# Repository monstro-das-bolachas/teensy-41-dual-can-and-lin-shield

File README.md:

# OBDee-Wan CANobi

> Open-hardware automotive bus interface for CAN FD, classic CAN, LIN, and K-line exploration.

OBDee-Wan CANobi is a Teensy 4.1 based vehicle-network tool for hackers, makers, reverse engineers, EV converters, and curious learners who want hardware they can inspect and understand.

It is designed as a practical bridge between a laptop and a vehicle or bench module: powerful enough for real CAN FD/LIN/K-line experiments, but documented as a teaching project rather than a black box.

## At a glance

| Area | Current R11 target |
| --- | --- |
| Host | Teensy 4.1 |
| CAN FD | 2 external CAN FD controller paths |
| Transceivers | Dual CAN FD transceivers |
| Other buses | LIN / K-line support path |
| Vehicle connection | OBD pigtail-friendly wiring, not a direct-plug dongle |
| Configuration | DIP-switch selectable routing options |
| CAD | KiCad hardware source and generated fabrication packages |
| Readiness | Bare-PCB prototype candidate for bench bring-up |

## What you can use it for

- CAN FD experimentation and learning
- Classic CAN diagnostics and reverse engineering
- LIN and K-line bench experiments
- EV conversion support tooling
- Custom diagnostic interface development
- Teaching automotive networks with inspectable hardware
- Bench testing ECUs, modules, sensors, and harness fragments

## Current status: R11 prototype manufacturing candidate

R11 may be ordered as a small bare-PCB prototype batch for bench bring-up.

It is not approved for direct vehicle testing yet.

### Active release package

`revisions/00_WORK_R11_TRUE_DUAL_CANFD/release/R11_PROTOTYPE_MANUFACTURING_CANDIDATE_20260630/`

### Manufacturer upload ZIP

`revisions/00_WORK_R11_TRUE_DUAL_CANFD/release/R11_PROTOTYPE_MANUFACTURING_CANDIDATE_20260630/package/JLCPCB_PCBWAY_UPLOAD_R11_MINIMAL_GERBERS_ONLY_20260630.zip`

SHA256:

`434dedf475bb3443f1ffa6384541426fcef9cf96a792c1744b9c1bb7ff68faa8`

### Verification summary

| Check | Result |
| --- | --- |
| KiCad CLI PCB DRC | 0 violations |
| Footprint errors | 0 |
| Known residual | 1 GND zone-to-zone report at 1.0000 mm / 1.0000 mm |
| Gerber/drill export | Successful |
| GND continuity | Visually confirmed in KiCad after refill/highlight |
| Vehicle-use approval | Not yet; bench validation required first |

The remaining GND item is a reviewed KiCad zone-report artifact for prototype PCB ordering. It is not a blanket safety approval for vehicle connection.

## Safety first

Vehicle electrical systems can damage tools, modules, or the car if connected incorrectly. Treat every first assembly as experimental hardware.

Before connecting to a vehicle:

1. Inspect the bare PCB.
2. Check for rail shorts with a multimeter.
3. Assemble and test the power section first.
4. Power up from a current-limited bench supply.
5. Verify OBD/pigtail pin mapping manually.
6. Confirm DIP-switch defaults and intended routing.
7. Test CAN/LIN/K behavior on bench modules first.
8. Use fusing and current limiting for any later vehicle test.

## Repository map

| Path | Purpose |
| --- | --- |
| `README_START_HERE.txt` | Short navigation and safety guide |
| `CURRENT_STATUS.md` | Current revision status, ordering notes, and verification summary |
| `revisions/00_WORK_R11_TRUE_DUAL_CANFD/` | Active R11 prototype candidate source and release package |
| `revisions/00_ACTIVE_R10_TRUE_DUAL_CANFD/` | Previous R10 archive, not for fabrication |
| `revisions/01_R9_CLASSIC_CAN_ARCHIVE/` | Historical R9 classic-CAN reference |
| `LICENSE` | Main hardware license: CERN-OHL-P-2.0 |
| `LICENSES/` | Full license texts and license split documentation |

## Recommended first order

For the first prototype batch, use conservative bare-board settings:

| Option | Recommendation |
| --- | --- |
| Quantity | 5 or smallest economical batch |
| Layers | 2 |
| Material | FR-4 |
| Thickness | 1.6 mm |
| Copper | 1 oz |
| Surface finish | Standard low-cost prototype finish is acceptable |
| Electrical test | Yes |
| Assembly | No; hand-assemble and validate first |

## Naming note

The project name is a small joke:

OBDee-Wan CANobi: an OBD/CAN interface that helps you feel disturbances in the bus.

## License

This project is open source and open hardware.

| Content | License |
| --- | --- |
| Hardware design files, KiCad sources, PCB/manufacturing files | CERN-OHL-P-2.0 |
| Firmware, scripts, and software | MIT |
| Documentation | CC-BY-4.0 |

You are free to study, modify, build, remix, and share this project. Attribution is required where applicable: please credit the original project and author when reusing or publishing derivative work.

See `LICENSES/README.md` for the full license split and SPDX identifiers.

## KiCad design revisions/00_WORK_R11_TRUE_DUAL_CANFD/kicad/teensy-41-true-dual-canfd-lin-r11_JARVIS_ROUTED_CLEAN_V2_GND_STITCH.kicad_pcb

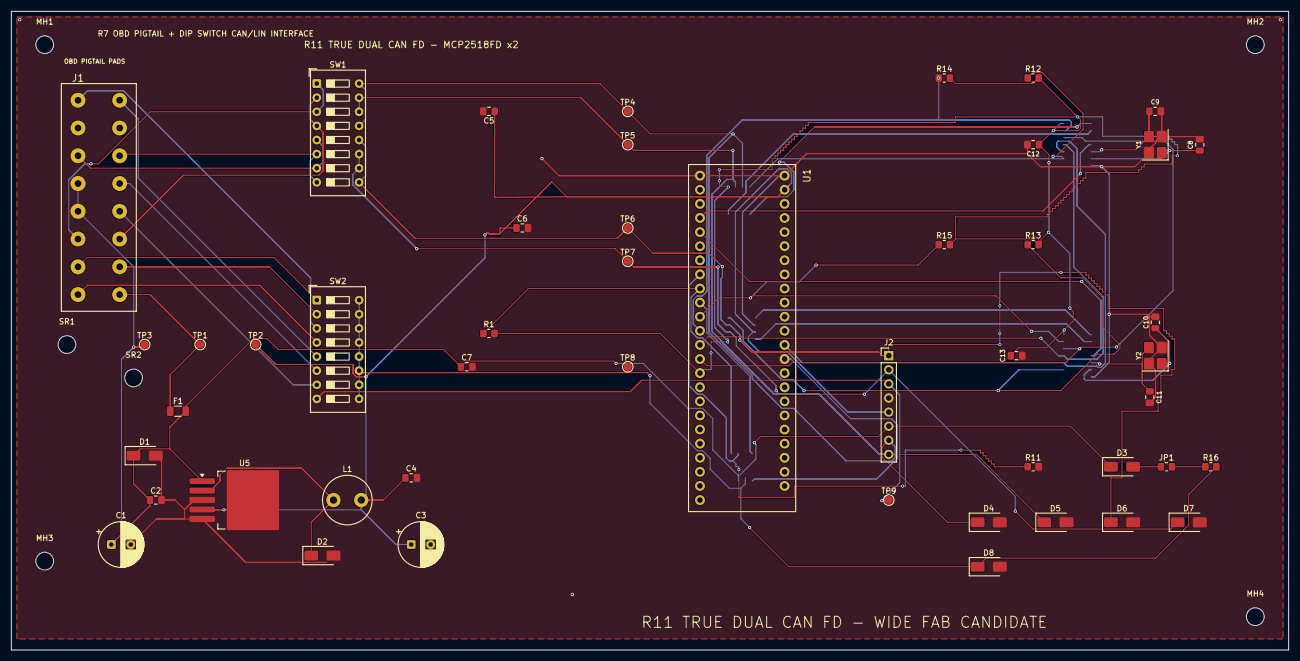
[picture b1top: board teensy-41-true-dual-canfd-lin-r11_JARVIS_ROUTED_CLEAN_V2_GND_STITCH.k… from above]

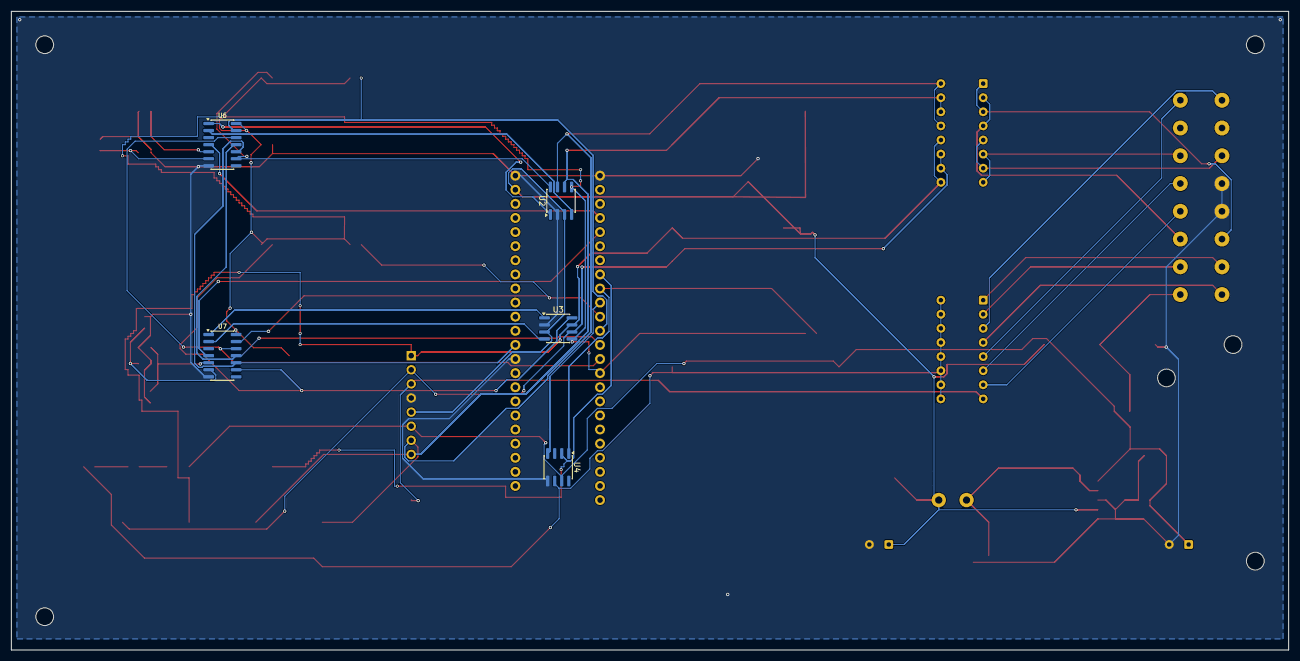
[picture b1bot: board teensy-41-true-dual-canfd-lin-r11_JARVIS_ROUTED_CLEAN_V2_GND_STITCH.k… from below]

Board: 2 copper layers, 230.0 x 115.0 mm, 59 parts (5 on the bottom side), 45 nets.

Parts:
C1: 100uF_50V_INPUT; CP_Radial_D8.0mm_P3.50mm
C2: 100nF_50V_INPUT; C_0805_2012Metric_Pad1.18x1.45mm_HandSolder
C3: 330uF_16V_OUTPUT_LOW_ESR; CP_Radial_D8.0mm_P3.50mm
C4: 100nF_16V_OUTPUT; C_0805_2012Metric_Pad1.18x1.45mm_HandSolder
C5: 100nF_CAN_A_VDD_LOCAL; C_0805_2012Metric_Pad1.18x1.45mm_HandSolder
C6: 100nF_CAN_B_VDD_LOCAL; C_0805_2012Metric_Pad1.18x1.45mm_HandSolder
C7: 100nF_LIN_VSUP_LOCAL; C_0805_2012Metric_Pad1.18x1.45mm_HandSolder
C8: 22pF_Y1_OSC1; C_0805_2012Metric_Pad1.18x1.45mm_HandSolder
C9: 22pF_Y1_OSC2; C_0805_2012Metric_Pad1.18x1.45mm_HandSolder
C10: 22pF_Y2_OSC1; C_0805_2012Metric_Pad1.18x1.45mm_HandSolder
C11: 22pF_Y2_OSC2; C_0805_2012Metric_Pad1.18x1.45mm_HandSolder
C12: 100nF_U6_VDD_LOCAL; C_0805_2012Metric_Pad1.18x1.45mm_HandSolder
C13: 100nF_U7_VDD_LOCAL; C_0805_2012Metric_Pad1.18x1.45mm_HandSolder
D1: SMBJ24CA_TVS_12V; D_SMA
D2: SS34_BUCK_SCHOTTKY; D_SMA
D3: LIN_MASTER_PULLUP_DIODE_DNP; D_SMA
D4: ESD_CAN_A_H_TVS_VERIFY; D_SMA
D5: ESD_CAN_A_L_TVS_VERIFY; D_SMA
D6: ESD_CAN_B_H_TVS_VERIFY; D_SMA
D7: ESD_CAN_B_L_TVS_VERIFY; D_SMA
D8: ESD_LIN_K_TVS_VERIFY; D_SMA
F1: POLYFUSE_500mA; Fuse_1206_3216Metric
J1: OBD2_PIGTAIL_16_WIRE_SOLDER_PADS; OBD2_PigtailPads_Manufacturing
J2: AUX_HEADER; PinHeader_1x08_P2.54mm_Vertical
JP1: LIN_MASTER_ENABLE_OPEN_0R_DNP; R_0805_2012Metric_Pad1.20x1.40mm_HandSolder
L1: 33uH_3A_BUCK_INDUCTOR; L_Radial_D8.7mm_P5.00mm_Fastron_07HCP
MH1, MH2, MH3, MH4: M3; MountingHole_3.2mm_M3
R1: 10k_LIN_RX_PULLUP; R_0805_2012Metric_Pad1.20x1.40mm_HandSolder
R11: 100k_LIN_EN_PULLDOWN; R_0805_2012Metric_Pad1.20x1.40mm_HandSolder
R12: 10k_CAN_A_STBY_PULLUP; R_0805_2012Metric_Pad1.20x1.40mm_HandSolder
R13: 10k_CAN_B_STBY_PULLUP; R_0805_2012Metric_Pad1.20x1.40mm_HandSolder
R14: 10k_CANFD_A_NCS_PULLUP; R_0805_2012Metric_Pad1.20x1.40mm_HandSolder
R15: 10k_CANFD_B_NCS_PULLUP; R_0805_2012Metric_Pad1.20x1.40mm_HandSolder
R16: 1k_LIN_MASTER_PULLUP_DNP; R_0805_2012Metric_Pad1.20x1.40mm_HandSolder
SR1, SR2: CABLE_STRAIN_RELIEF; MountingHole_3.2mm_M3
SW1: CAN_NORMAL_CROSS_DIP_8POS; SW_DIP_SPSTx08_Slide_9.78x22.5mm_W7.62mm_P2.54mm
SW2: LIN_K_SOURCE_DIP_8POS_SELECT_ONE; SW_DIP_SPSTx08_Slide_9.78x22.5mm_W7.62mm_P2.54mm
TP1: 12V; TestPoint_Pad_D1.5mm
TP2: 5V; TestPoint_Pad_D1.5mm
TP3: GND; TestPoint_Pad_D1.5mm
TP4: CAN_A_H; TestPoint_Pad_D1.5mm
TP5: CAN_A_L; TestPoint_Pad_D1.5mm
TP6: CAN_B_H; TestPoint_Pad_D1.5mm
TP7: CAN_B_L; TestPoint_Pad_D1.5mm
TP8: LIN_BUS; TestPoint_Pad_D1.5mm
TP9: AUX_LIN_K; TestPoint_Pad_D1.5mm
U1: TEENSY_4.1_MAIN_HEADERS_PJRC_AUDITED; Teensy_4.1_MainHeaders_PJRC_Audited
U2: MCP2562FD_CAN_A_3V3_IO; SOIC-8_3.9x4.9mm_P1.27mm
U3: MCP2562FD_CAN_B_3V3_IO; SOIC-8_3.9x4.9mm_P1.27mm
U4: TLIN1029DRQ1_LIN_3V3_LOGIC; SOIC-8_3.9x4.9mm_P1.27mm
U5: LM2596S-5.0_BUCK; TO-263-5_TabPin3
U6: MCP2518FD_A_SOIC14; SOIC-14_3.9x8.7mm_P1.27mm
U7: MCP2518FD_B_SOIC14; SOIC-14_3.9x8.7mm_P1.27mm
Y1, Y2: 40MHz_3225_VERIFY_CL; Crystal_SMD_3225-4Pin_3.2x2.5mm_HandSoldering

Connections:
+3V3: C12.1, C13.1, R1.2, R12.2, R13.2, R14.2, R15.2, U1.3V3_B, U2.5, U3.5, U6.14, U7.14
+5V_REGULATED: C3.1, C4.1, C5.1, C6.1, J2.5, L1.2, TP2.1, U1.VIN, U2.3, U3.3, U5.4
+12V_OBD: F1.1, J1.16, TP1.1
+12V_PROTECTED: C1.1, C2.1, C7.1, D1.1, D3.1, F1.2, J2.6, U4.7, U5.1
AUX_LIN_K_IO: J2.3, SW2.8, TP9.1
BUCK_SW: D2.1, L1.1, U5.2
CANFD_A_INT: U1.2, U6.4
CANFD_A_NCS: R14.1, U1.10, U6.13
CANFD_A_OSC1: C8.1, U6.6, Y1.1
CANFD_A_OSC2: C9.1, U6.5, Y1.3
CANFD_A_RXCAN: U2.4, U6.2
CANFD_A_TXCAN: U2.1, U6.1
CANFD_A_XSTBY: R12.1, U2.8, U6.9
CANFD_B_INT: U1.3, U7.4
CANFD_B_NCS: R15.1, U1.9, U7.13
CANFD_B_OSC1: C10.1, U7.6, Y2.1
CANFD_B_OSC2: C11.1, U7.5, Y2.3
CANFD_B_RXCAN: U3.4, U7.2
CANFD_B_TXCAN: U3.1, U7.1
CANFD_B_XSTBY: R13.1, U3.8, U7.9
CANFD_SPI_SCK: U1.13, U6.10, U7.10
CANFD_SPI_SDI_MOSI: U1.11, U6.11, U7.11
CANFD_SPI_SDO_MISO: U1.12, U6.12, U7.12
CAN_A_H: D4.1, J2.7, SW1.13, SW1.16, TP4.1, U2.7
CAN_A_L: D5.1, J2.8, SW1.14, SW1.15, TP5.1, U2.6
CAN_B_H: D6.1, J2.1, SW1.9, SW1.12, TP6.1, U3.7
CAN_B_L: D7.1, J2.2, SW1.10, SW1.11, TP7.1, U3.6
GND: C1.2, C2.2, C3.2, C4.2, C5.2, C6.2, C7.2, C8.2, C9.2, C10.2, C11.2, C12.2, C13.2, D1.2, D2.2, D4.2, D5.2, D6.2, D7.2, D8.2, J1.4, J1.5, J2.4, R11.2, TP3.1, U1.GND_B1, U1.GND_T1, U1.GND_T2, U2.2, U3.2, U4.5, U5.3, U5.5, U6.7, U7.7, Y1.2, Y1.4, Y2.2, Y2.4
LIN_BUS: D8.1, R16.2, SW2.9, SW2.10, SW2.11, SW2.12, SW2.13, SW2.14, SW2.15, SW2.16, TP8.1, U4.6
LIN_EN: R11.1, U1.6, U4.2
LIN_MASTER_DIODE_OUT: D3.2, JP1.1
LIN_MASTER_ENABLE: JP1.2, R16.1
LIN_RX: R1.1, U1.7, U4.1
LIN_TX: U1.8, U4.4
OBD1_SINGLE_WIRE_CANDIDATE: J1.1, SW2.3
OBD3_CAN_B_PAIR_A_CANDIDATE: J1.3, SW1.5, SW1.7
OBD6_CAN_A_PAIR_A: J1.6, SW1.1, SW1.3
OBD7_SINGLE_WIRE_CANDIDATE: J1.7, SW2.1
OBD8_SINGLE_WIRE_CANDIDATE: J1.8, SW2.4
OBD9_SINGLE_WIRE_CANDIDATE: J1.9, SW2.5
OBD11_CAN_B_PAIR_B_CANDIDATE: J1.11, SW1.6, SW1.8
OBD12_SINGLE_WIRE_CANDIDATE: J1.12, SW2.6
OBD13_SINGLE_WIRE_CANDIDATE: J1.13, SW2.7
OBD14_CAN_A_PAIR_B: J1.14, SW1.2, SW1.4
OBD15_SINGLE_WIRE_CANDIDATE: J1.15, SW2.2

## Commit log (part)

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2026-06-21 Add R5 pigtail DIP-switch manufacturing candidate
2026-06-21 Add R6 complete-power procurement candidate
2026-06-30 Mark R10 not for fabrication after review
2026-06-30 Publish R11 prototype manufacturing candidate
